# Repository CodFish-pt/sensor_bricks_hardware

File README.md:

# Internet of Things Sensor Brick (Base Project)

This is the series of sensors for IoT projects, made on base of the famous brick game. This is compatible to the format to be used with others bricks to prototype quickly.

This is the base project using the Bosch BMI160.

Sensor | Project Link
------------ | -------------
Bosch BMI160 | [Goto Project](https://github.com/pedrominatel/cf_sensor_brick_model)
Bosch BME680 | [Goto Project](https://github.com/CodFish-pt/sensor_bricks_hardware/tree/main/bme680)
STM LIS2DH | [Goto Project](https://github.com/CodFish-pt/sensor_bricks_hardware/tree/main/lis2dh12)

Happy Hacking!

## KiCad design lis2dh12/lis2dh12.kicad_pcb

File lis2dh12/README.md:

# STM LIS2DH Internet of Things Sensor Brick

This is the series of sensors for IoT projects, made on base of the famous brick game. This is compatible to the format to be used with others bricks to prototype quickly.

STM LIS2DH Sensor

Sensor | Project Link
------------ | -------------
Bosch BMI160 | [Goto Project](https://github.com/pedrominatel/cf_sensor_brick_model)
Bosch BME680 | [Goto Project](https://github.com/CodFish-pt/sensor_bricks_hardware/tree/main/bme680) 
STM LIS2DH | [Goto Project](https://github.com/CodFish-pt/sensor_bricks_hardware/tree/main/lis2dh12)

Happy Hacking!

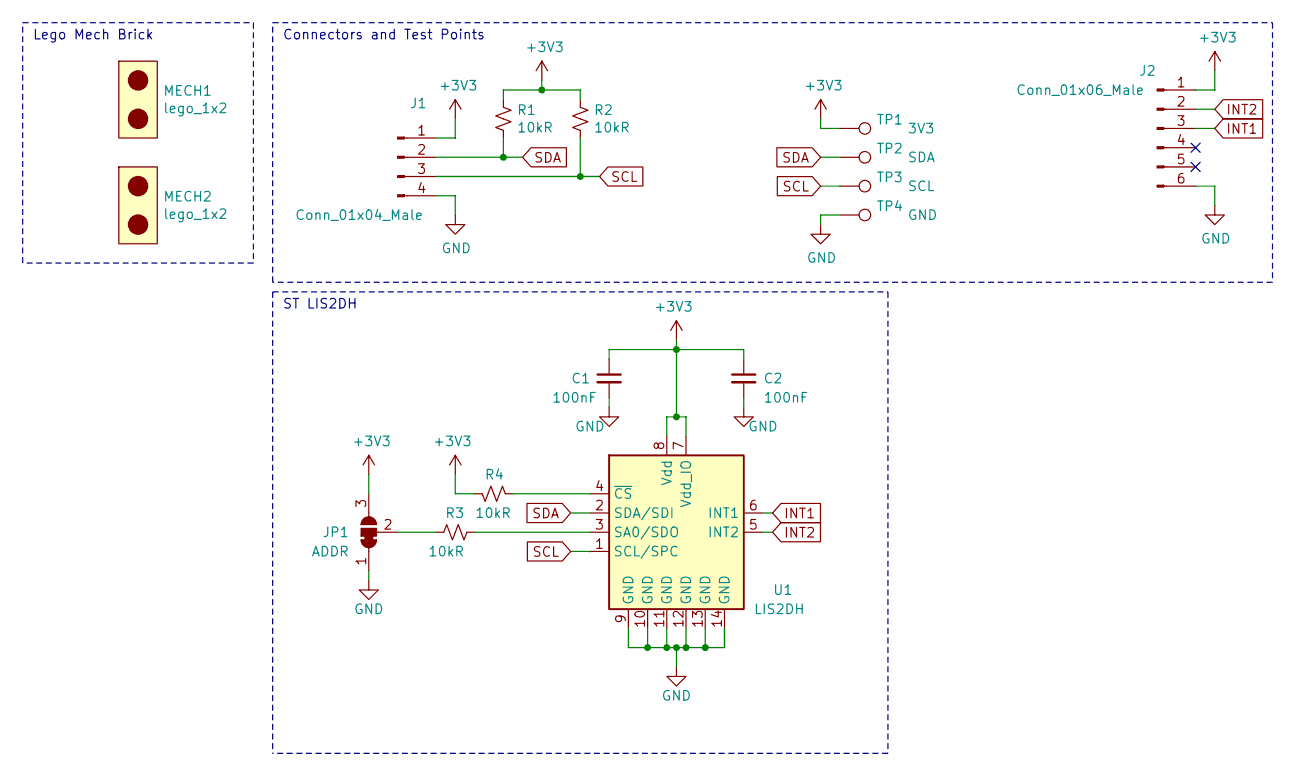
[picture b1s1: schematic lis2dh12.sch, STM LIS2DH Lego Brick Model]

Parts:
C1, C2: 100nF; C_0603_1608Metric
J1: Conn_01x04_Male; PinHeader_1x04_P2.00mm_Vertical
J2: Conn_01x06_Male; PinHeader_1x06_P2.00mm_Vertical
JP1: ADDR; SolderJumper-3_P1.3mm_Bridged12_RoundedPad1.0x1.5mm
MECH1, MECH2: lego_1x2
R1, R2, R3, R4: 10kR; R_0603_1608Metric
TP1: 3V3; TestPoint_Pad_D2.5mm
TP2: SDA; TestPoint_Pad_D2.5mm
TP3: SCL; TestPoint_Pad_D2.5mm
TP4: GND; TestPoint_Pad_D2.5mm
U1: LIS2DH; LGA-14_2x2mm_P0.35mm_LayoutBorder3x4y

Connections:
+3V3: C1.1, C2.1, J1.1, J2.1, JP1.3 (B), R1.1, R2.1, R4.2, TP1.1, U1.7 (Vdd_IO), U1.8 (Vdd)
GND: C1.2, C2.2, J1.4, J2.6, JP1.1 (A), TP4.1, U1.9 (GND), U1.10 (GND), U1.11 (GND), U1.12 (GND), U1.13 (GND), U1.14 (GND)
INT1: J2.3, U1.6 (INT1)
INT2: J2.2, U1.5 (INT2)
unnamed: JP1.2 (C), R3.1
unnamed: R3.2, U1.3 (SA0/SDO)
unnamed: R4.1, U1.4 (~CS)
SCL: J1.3, R2.2, TP3.1, U1.1 (SCL/SPC)
SDA: J1.2, R1.2, TP2.1, U1.2 (SDA/SDI)

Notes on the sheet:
ST LIS2DH
Lego Mech Brick
Connectors and Test Points

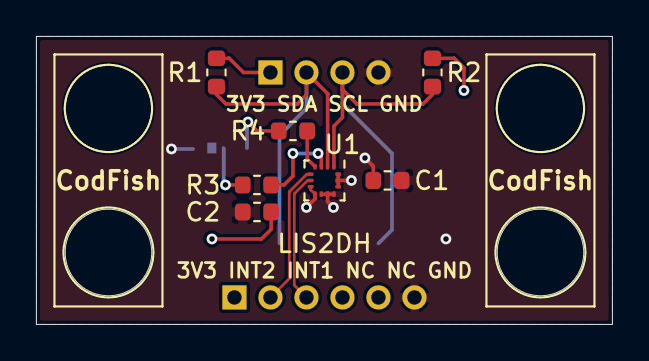
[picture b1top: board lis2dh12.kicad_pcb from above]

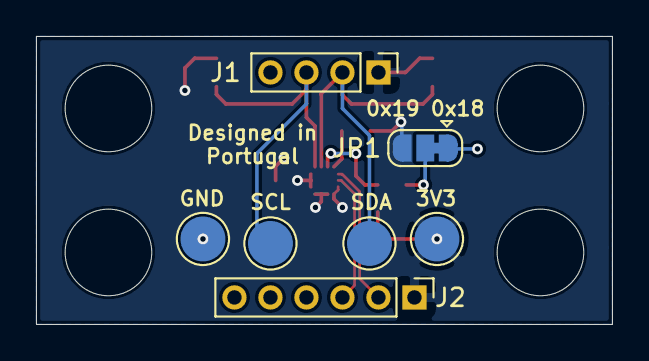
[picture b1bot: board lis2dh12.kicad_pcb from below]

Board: 2 copper layers, 32.0 x 16.0 mm, 16 parts (7 on the bottom side), 9 nets.

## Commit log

2020-10-17 Added submodule to the main sensors repo
2020-10-17 Readme.md updated
2020-10-17 Added BME680 sensor and BMI160 updated
2020-10-17 Added LIS2DH sensor
